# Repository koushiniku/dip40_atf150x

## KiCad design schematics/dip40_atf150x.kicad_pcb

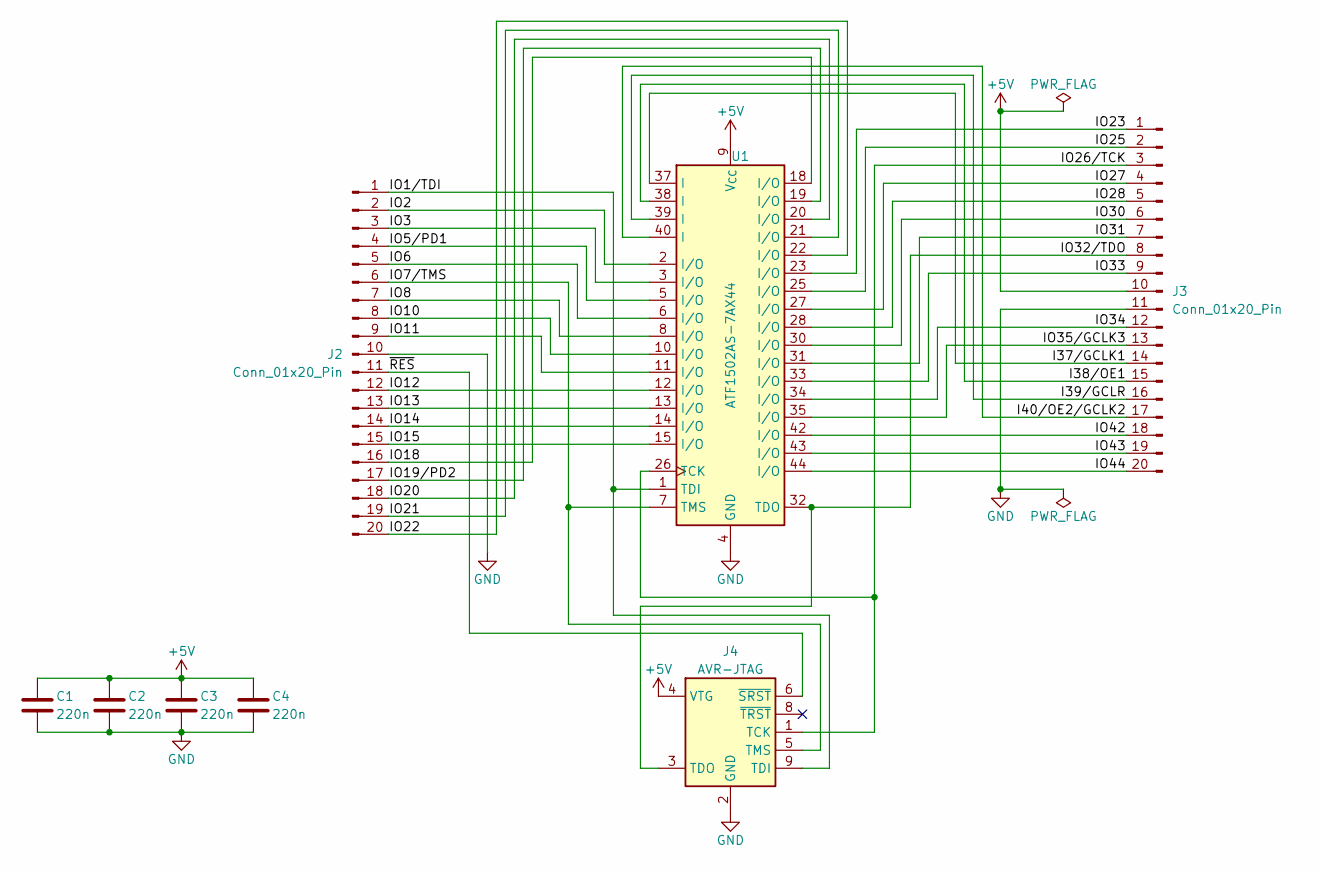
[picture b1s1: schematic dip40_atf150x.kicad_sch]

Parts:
C1, C2, C3, C4: 220n; C_0402
J2, J3: Conn_01x20_Pin; PinHeader_1x20_P2.54mm_Vertical
J4: AVR-JTAG; PinHeader_2x05_P2.54mm_Vertical
U1: ATF1502AS-7AX44; TQFP-44-1EP_10x10mm_P0.8mm_EP4.5x4.5mm

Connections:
+5V: C1.1, C2.1, C3.1, C4.1, J3.10, J4.4 (VTG), U1.9 (V_{CC}), U1.17 (V_{CC}), U1.29 (V_{CC}), U1.41 (V_{CC})
/I37/GCLK1: J3.14, U1.37 (I)
/I38/OE1: J3.15, U1.38 (I)
/I39/GCLR: J3.16, U1.39 (I)
/I40/OE2/GCLK2: J3.17, U1.40 (I)
/IO1/TDI: J2.1, J4.9 (TDI), U1.1 (TDI)
/IO2: J2.2, U1.2 (I/O)
/IO3: J2.3, U1.3 (I/O)
/IO5/PD1: J2.4, U1.5 (I/O)
/IO6: J2.5, U1.6 (I/O)
/IO7/TMS: J2.6, J4.5 (TMS), U1.7 (TMS)
/IO8: J2.7, U1.8 (I/O)
/IO10: J2.8, U1.10 (I/O)
/IO11: J2.9, U1.11 (I/O)
/IO12: J2.12, U1.12 (I/O)
/IO13: J2.13, U1.13 (I/O)
/IO14: J2.14, U1.14 (I/O)
/IO15: J2.15, U1.15 (I/O)
/IO18: J2.16, U1.18 (I/O)
/IO19/PD2: J2.17, U1.19 (I/O)
/IO20: J2.18, U1.20 (I/O)
/IO21: J2.19, U1.21 (I/O)
/IO22: J2.20, U1.22 (I/O)
/IO23: J3.1, U1.23 (I/O)
/IO25: J3.2, U1.25 (I/O)
/IO26/TCK: J3.3, J4.1 (TCK), U1.26 (TCK)
/IO27: J3.4, U1.27 (I/O)
/IO28: J3.5, U1.28 (I/O)
/IO30: J3.6, U1.30 (I/O)
/IO31: J3.7, U1.31 (I/O)
/IO32/TDO: J3.8, J4.3 (TDO), U1.32 (TDO)
/IO33: J3.9, U1.33 (I/O)
/IO34: J3.12, U1.34 (I/O)
/IO35/GCLK3: J3.13, U1.35 (I/O)
/IO42: J3.18, U1.42 (I/O)
/IO43: J3.19, U1.43 (I/O)
/IO44: J3.20, U1.44 (I/O)
/~RES: J2.11, J4.6 (~SRST)
GND: C1.2, C2.2, C3.2, C4.2, J2.10, J3.11, J4.2 (GND), J4.10 (GND), U1.4 (GND), U1.16 (GND), U1.24 (GND), U1.36 (GND)

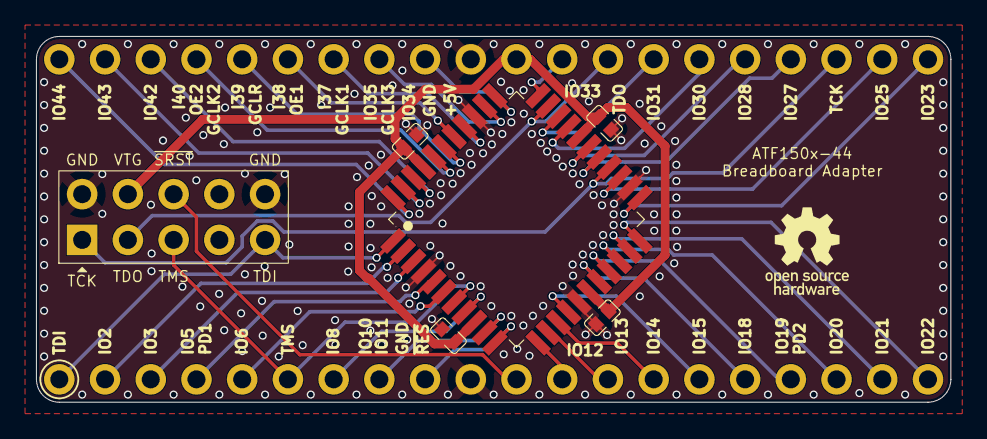
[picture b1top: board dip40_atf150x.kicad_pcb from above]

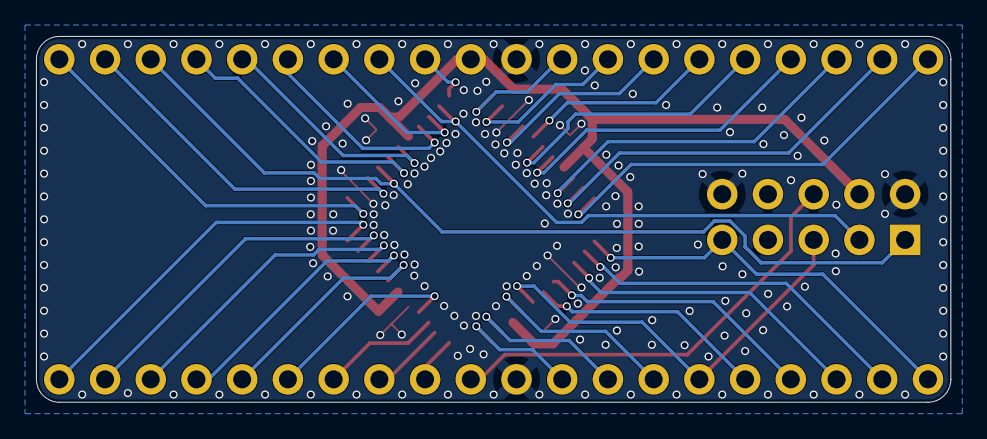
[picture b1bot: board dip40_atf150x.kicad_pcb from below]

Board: 2 copper layers, 50.8 x 20.3 mm, 8 parts (2 on the bottom side), 39 nets.
